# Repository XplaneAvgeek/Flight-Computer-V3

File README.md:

Flight Computer V3 is the third version of model rocket flight computers I've been trying to build. It's designed to control a guided model rocket, and improve things from V2.
<br><br>Some specs about it are:
  - Input Voltage: 6-17V
  - Uses a STM32H743VIH6 microcontroller
  - 4 MOSFETs connected to battery input, I recommend use it for less than 3A
  - 5V power regulator that can regulate 5A using a TPS565208DDCR
  - Should have reverse polarity protection (NOT TESTED)
  - IMU: LSM6DSO32, which is 6 axis
  - Barometer: LPS22HB
  - Magnetometer: IIS2MDC
  - Flash Memory: W25Q256JVEIQ TR, which is 32MB
  - Programming methods: ST-LINK V2, FS USB-C
  - Onboard Indication: 2 addressable RGB LEDs
  - Communication outside board: SPI, I2C, FDCAN, USART
  - Has 8 servo connectors at 5V but total 5V max is 5A

<br><br>[Here is the link to the code in Arduino Framework.](FlightComputerV3_Setup)
<br>[Here is the link to the KiCad design files.](Flight_Computer_V2_Proto2)

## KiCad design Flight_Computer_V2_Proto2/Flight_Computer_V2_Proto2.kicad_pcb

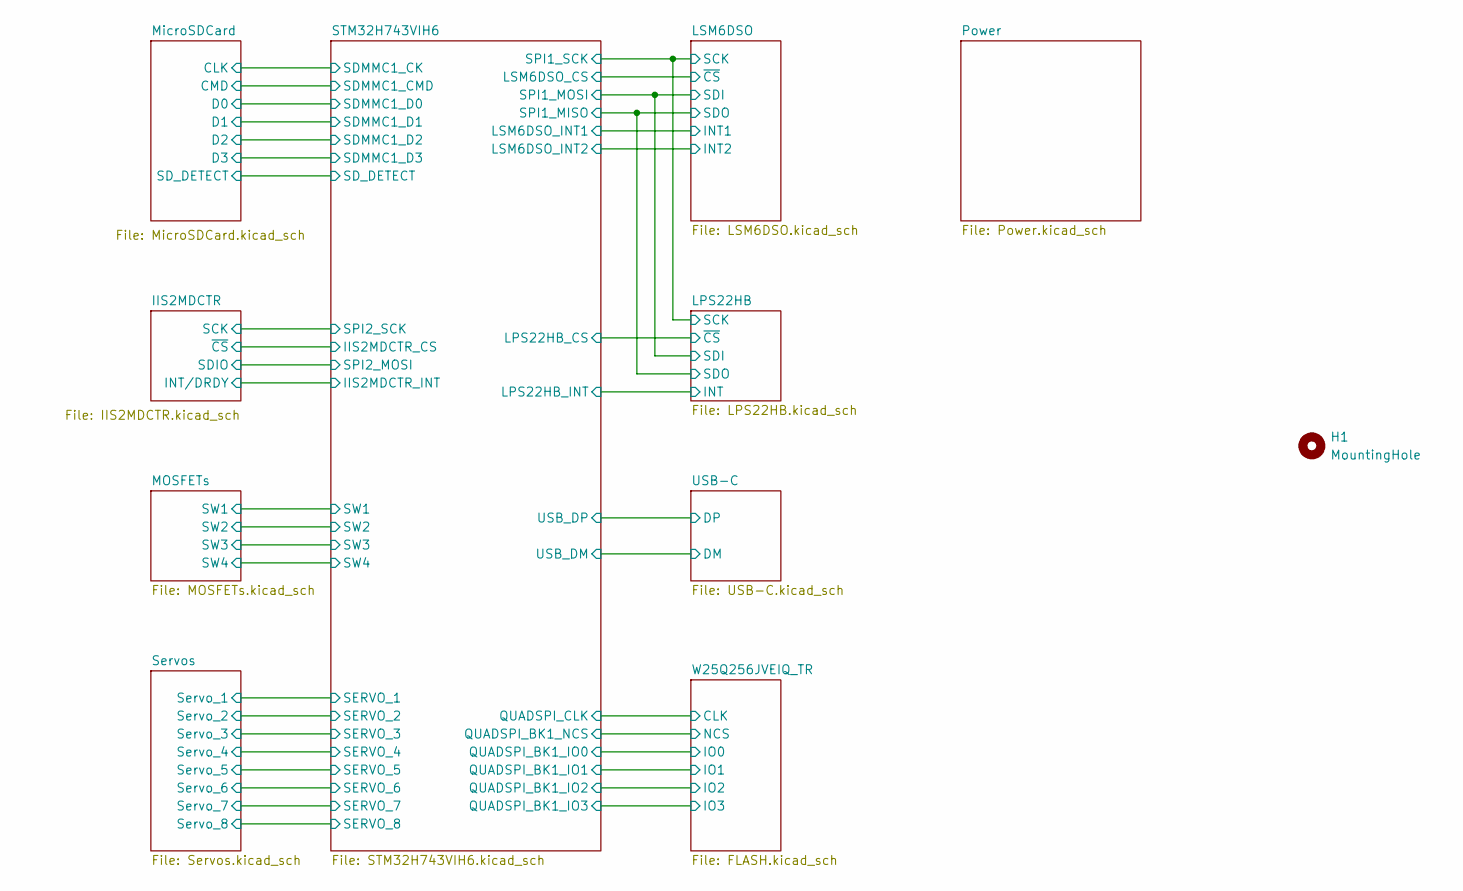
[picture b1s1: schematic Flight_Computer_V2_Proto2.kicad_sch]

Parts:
H1: MountingHole; logo15x15mmv3

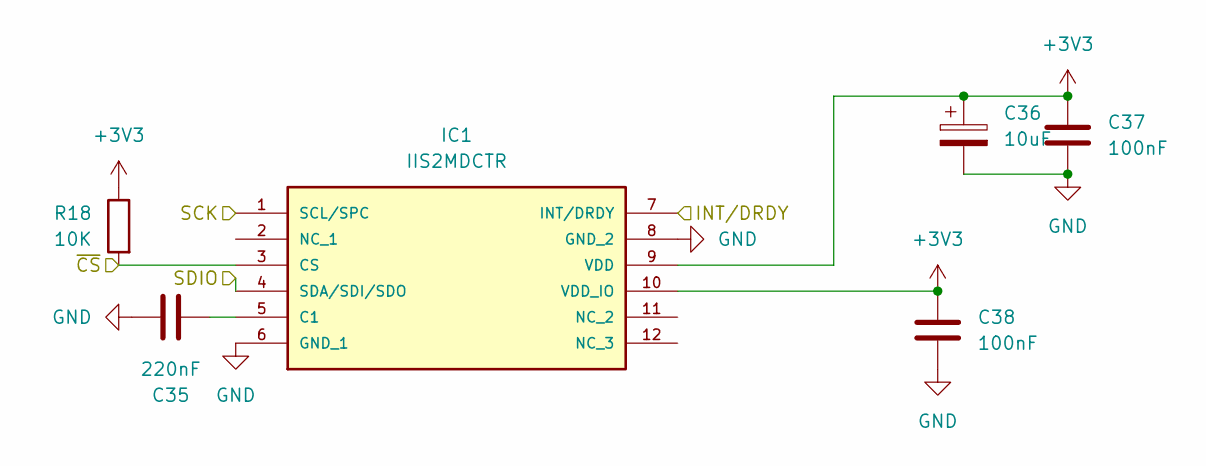
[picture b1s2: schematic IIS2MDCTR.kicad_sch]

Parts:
C35: 220nF; C_0402_1005Metric
C36: 10uF; CP_Elec_4x5.3
C37, C38: 100nF; C_0402_1005Metric
IC1: IIS2MDCTR; LGA-12_2x2mm_P0.5mm; MOUSER_PART_NUMBER 511-IIS2MDCTR
R18: 10K; R_0402_1005Metric

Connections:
+3V3: C36.1, C37.1, C38.1, IC1.9 (VDD), IC1.10 (VDD_IO), R18.1; also elsewhere on the board
/IIS2MDCTR/INT/DRDY: IC1.7 (INT/DRDY); also elsewhere on the board
/IIS2MDCTR/SCK: IC1.1 (SCL/SPC); also elsewhere on the board
/IIS2MDCTR/SDIO: IC1.4 (SDA/SDI/SDO); also elsewhere on the board
/IIS2MDCTR/~CS: IC1.3 (CS), R18.2; also elsewhere on the board
GND: C35.1, C36.2, C37.2, C38.2, IC1.6 (GND_1), IC1.8 (GND_2); also elsewhere on the board
unnamed: C35.2, IC1.5 (C1)

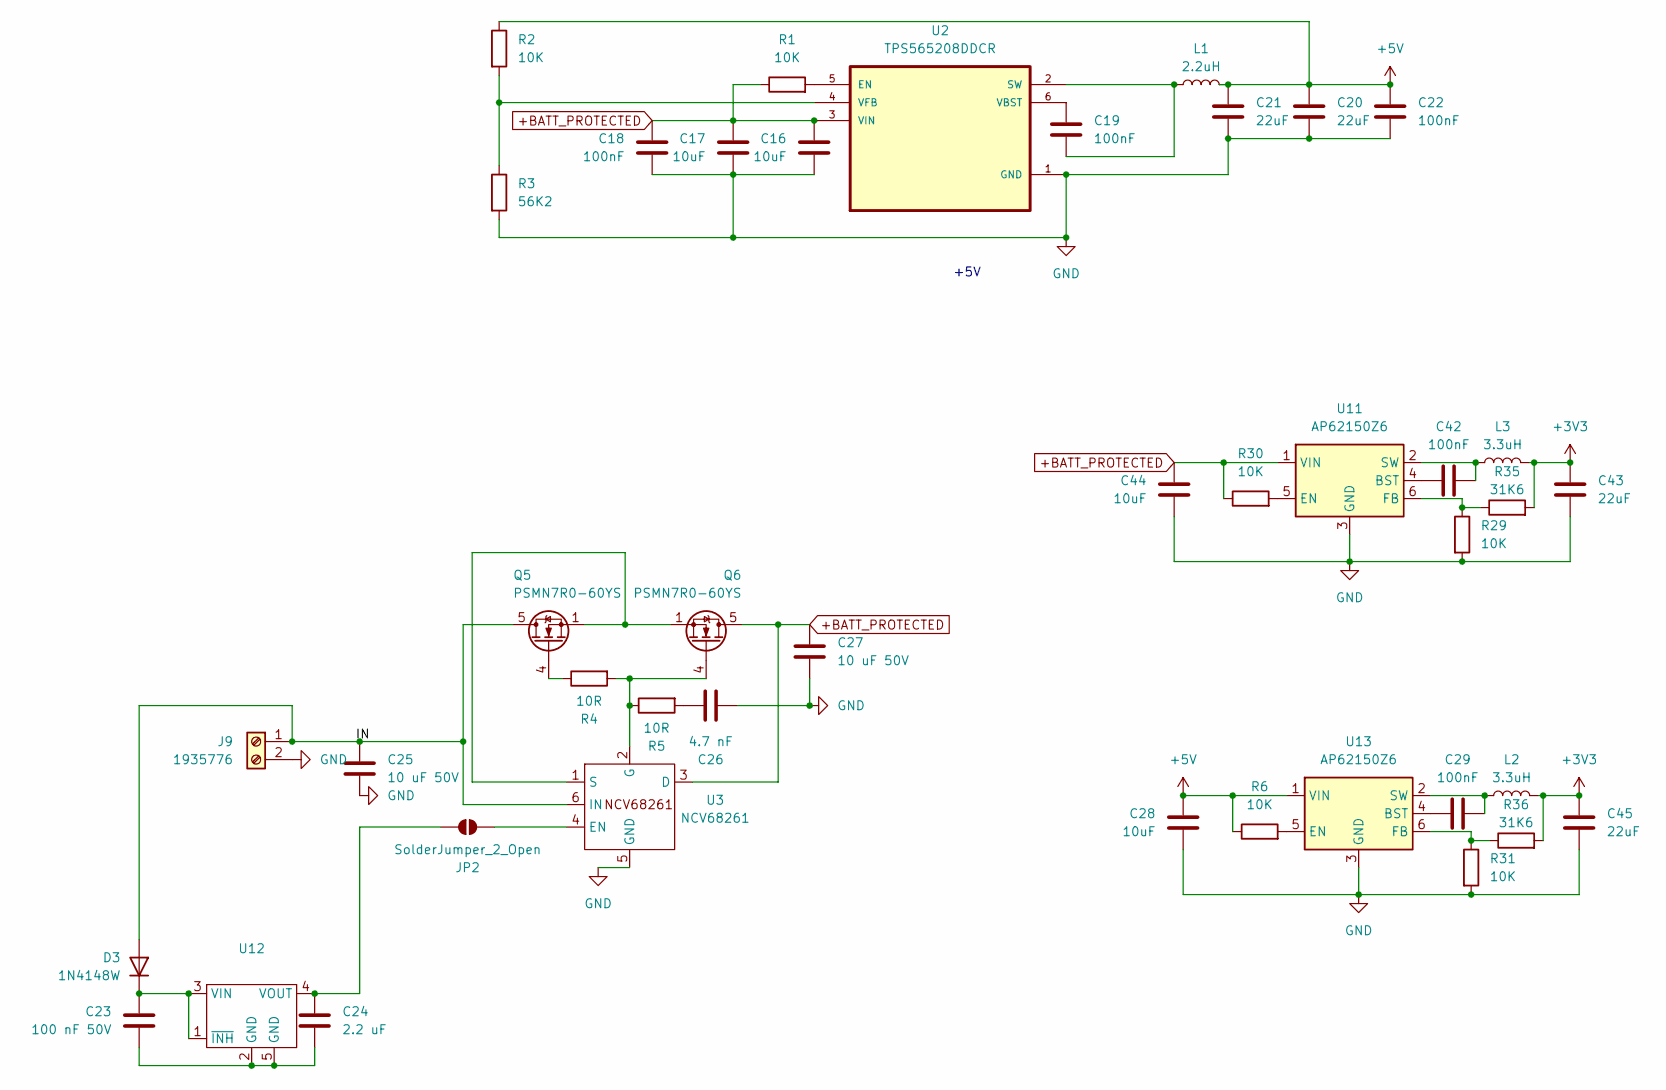
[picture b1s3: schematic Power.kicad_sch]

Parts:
C16, C17, C28, C44: 10uF; C_1206_3216Metric
C18, C19, C22, C29, C42: 100nF; C_0402_1005Metric
C20, C21, C43, C45: 22uF; C_1206_3216Metric
C23: 100 nF 50V; C_0603_1608Metric
C24: 2.2 uF; C_0805_2012Metric
C25, C27: 10 uF 50V; C_1206_3216Metric
C26: 4.7 nF; C_0603_1608Metric
D3: 1N4148W; D_SOD-123
J9: 1935776; PHOENIX_1935776
JP2: SolderJumper_2_Open; SolderJumper-2_P1.3mm_Open_TrianglePad1.0x1.5mm
L1: 2.2uH; L_Bourns_SRP5030T
L2, L3: 3.3uH; L_1008_2520Metric
Q5, Q6: PSMN7R0-60YS; LFPAK56
R1, R2, R6, R29, R30, R31: 10K; R_0402_1005Metric
R3: 56K2; R_0402_1005Metric
R4, R5: 10R; R_0603_1608Metric
R35, R36: 31K6; R_0402_1005Metric
U2: TPS565208DDCR; SOT95P280X110-6N
U3: NCV68261; DFN-6-1EP_2x2mm_P0.65mm_EP1x1.6mm
U11, U13: AP62150Z6; SOT-563
U12: NCV4296-2CSN50T1G; TSOP-5_1.65x3.05mm_P0.95mm

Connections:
+3V3: C43.1, C45.1, L2.2, L3.2, R35.2, R36.2; also elsewhere on the board
+5V: C20.1, C21.1, C22.1, C28.1, L1.2, R2.1, R6.1, U13.1 (VIN); also elsewhere on the board
+BATT_PROTECTED: C16.1, C17.1, C18.1, C27.1, C44.1, Q6.5 (D), R1.1, R30.1, U2.3 (VIN), U3.3 (D), U11.1 (VIN); also elsewhere on the board
/Power/IN: C25.1, D3.2 (A), J9.1, Q5.5 (D), U3.6 (IN)
GND: C16.2, C17.2, C18.2, C20.2, C21.2, C22.2, C25.2, C26.2, C27.2, C28.2, C43.2, C44.2, C45.2, J9.2, R3.2, R29.2, R31.2, U2.1 (GND), U3.5 (GND), U11.3 (GND), U13.3 (GND); also elsewhere on the board
unnamed: C23.2, C24.2, U12.2 (GND), U12.5 (GND)
unnamed: C26.1, R5.2
unnamed: C23.1, D3.1 (K), U12.1 (~INH), U12.3 (VIN)
unnamed: JP2.1 (A), U3.4 (EN)
unnamed: C24.1, JP2.2 (B), U12.4 (VOUT)
unnamed: Q5.4 (G), R4.1
unnamed: Q6.4 (G), R4.2, R5.1, U3.2 (G)
unnamed: R1.2, U2.5 (EN)
unnamed: C19.2, L1.1, U2.2 (SW)
unnamed: C19.1, U2.6 (VBST)
unnamed: R2.2, R3.1, U2.4 (VFB)
unnamed: Q5.1 (S), Q5.2 (S), Q5.3 (S), Q6.1 (S), Q6.2 (S), Q6.3 (S), U3.1 (S)
unnamed: C42.1, U11.4 (BST)
unnamed: R30.2, U11.5 (EN)
unnamed: R29.1, R35.1, U11.6 (FB)
unnamed: C42.2, L3.1, U11.2 (SW)
unnamed: C29.1, U13.4 (BST)
unnamed: R6.2, U13.5 (EN)
unnamed: R31.1, R36.1, U13.6 (FB)
unnamed: C29.2, L2.1, U13.2 (SW)

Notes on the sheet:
+5V

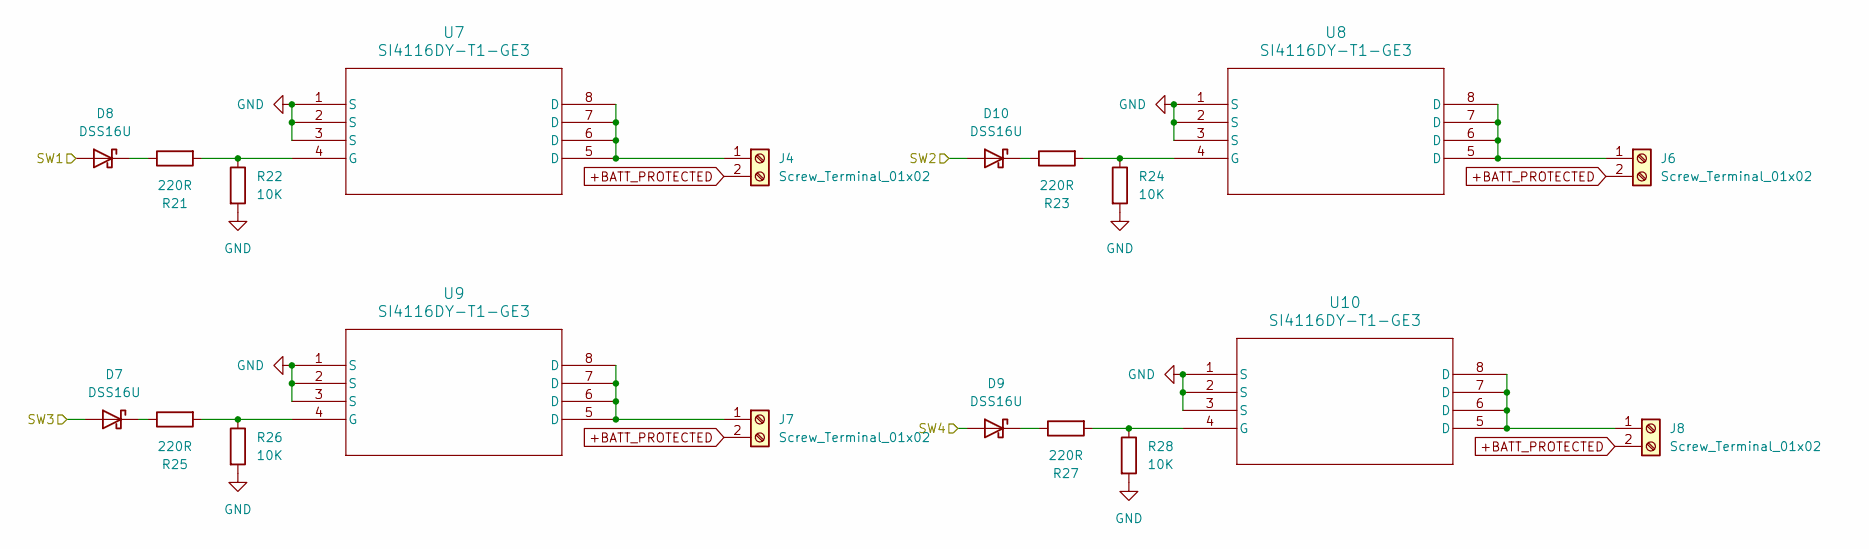
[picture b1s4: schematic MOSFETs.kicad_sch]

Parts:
D7, D8, D9, D10: DSS16U; D_SOD-123F
J4, J6, J7, J8: Screw_Terminal_01x02; PHOENIX_1935776
R21, R23, R25, R27: 220R; R_0402_1005Metric
R22, R24, R26, R28: 10K; R_0402_1005Metric
U7, U8, U9, U10: SI4116DY-T1-GE3; SOIC-8_3.9x4.9mm_P1.27mm

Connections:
+BATT_PROTECTED: J4.2, J6.2, J7.2, J8.2; also elsewhere on the board
/MOSFETs/SW1: D8.2 (A); also elsewhere on the board
/MOSFETs/SW2: D10.2 (A); also elsewhere on the board
/MOSFETs/SW3: D7.2 (A); also elsewhere on the board
/MOSFETs/SW4: D9.2 (A); also elsewhere on the board
GND: R22.2, R24.2, R26.2, R28.2, U7.1 (S), U7.2 (S), U7.3 (S), U8.1 (S), U8.2 (S), U8.3 (S), U9.1 (S), U9.2 (S), U9.3 (S), U10.1 (S), U10.2 (S), U10.3 (S); also elsewhere on the board
unnamed: D7.1 (K), R25.1
unnamed: D8.1 (K), R21.1
unnamed: D9.1 (K), R27.1
unnamed: D10.1 (K), R23.1
unnamed: J4.1, U7.5 (D), U7.6 (D), U7.7 (D), U7.8 (D)
unnamed: J6.1, U8.5 (D), U8.6 (D), U8.7 (D), U8.8 (D)
unnamed: J7.1, U9.5 (D), U9.6 (D), U9.7 (D), U9.8 (D)
unnamed: J8.1, U10.5 (D), U10.6 (D), U10.7 (D), U10.8 (D)
unnamed: R21.2, R22.1, U7.4 (G)
unnamed: R23.2, R24.1, U8.4 (G)
unnamed: R25.2, R26.1, U9.4 (G)
unnamed: R27.2, R28.1, U10.4 (G)

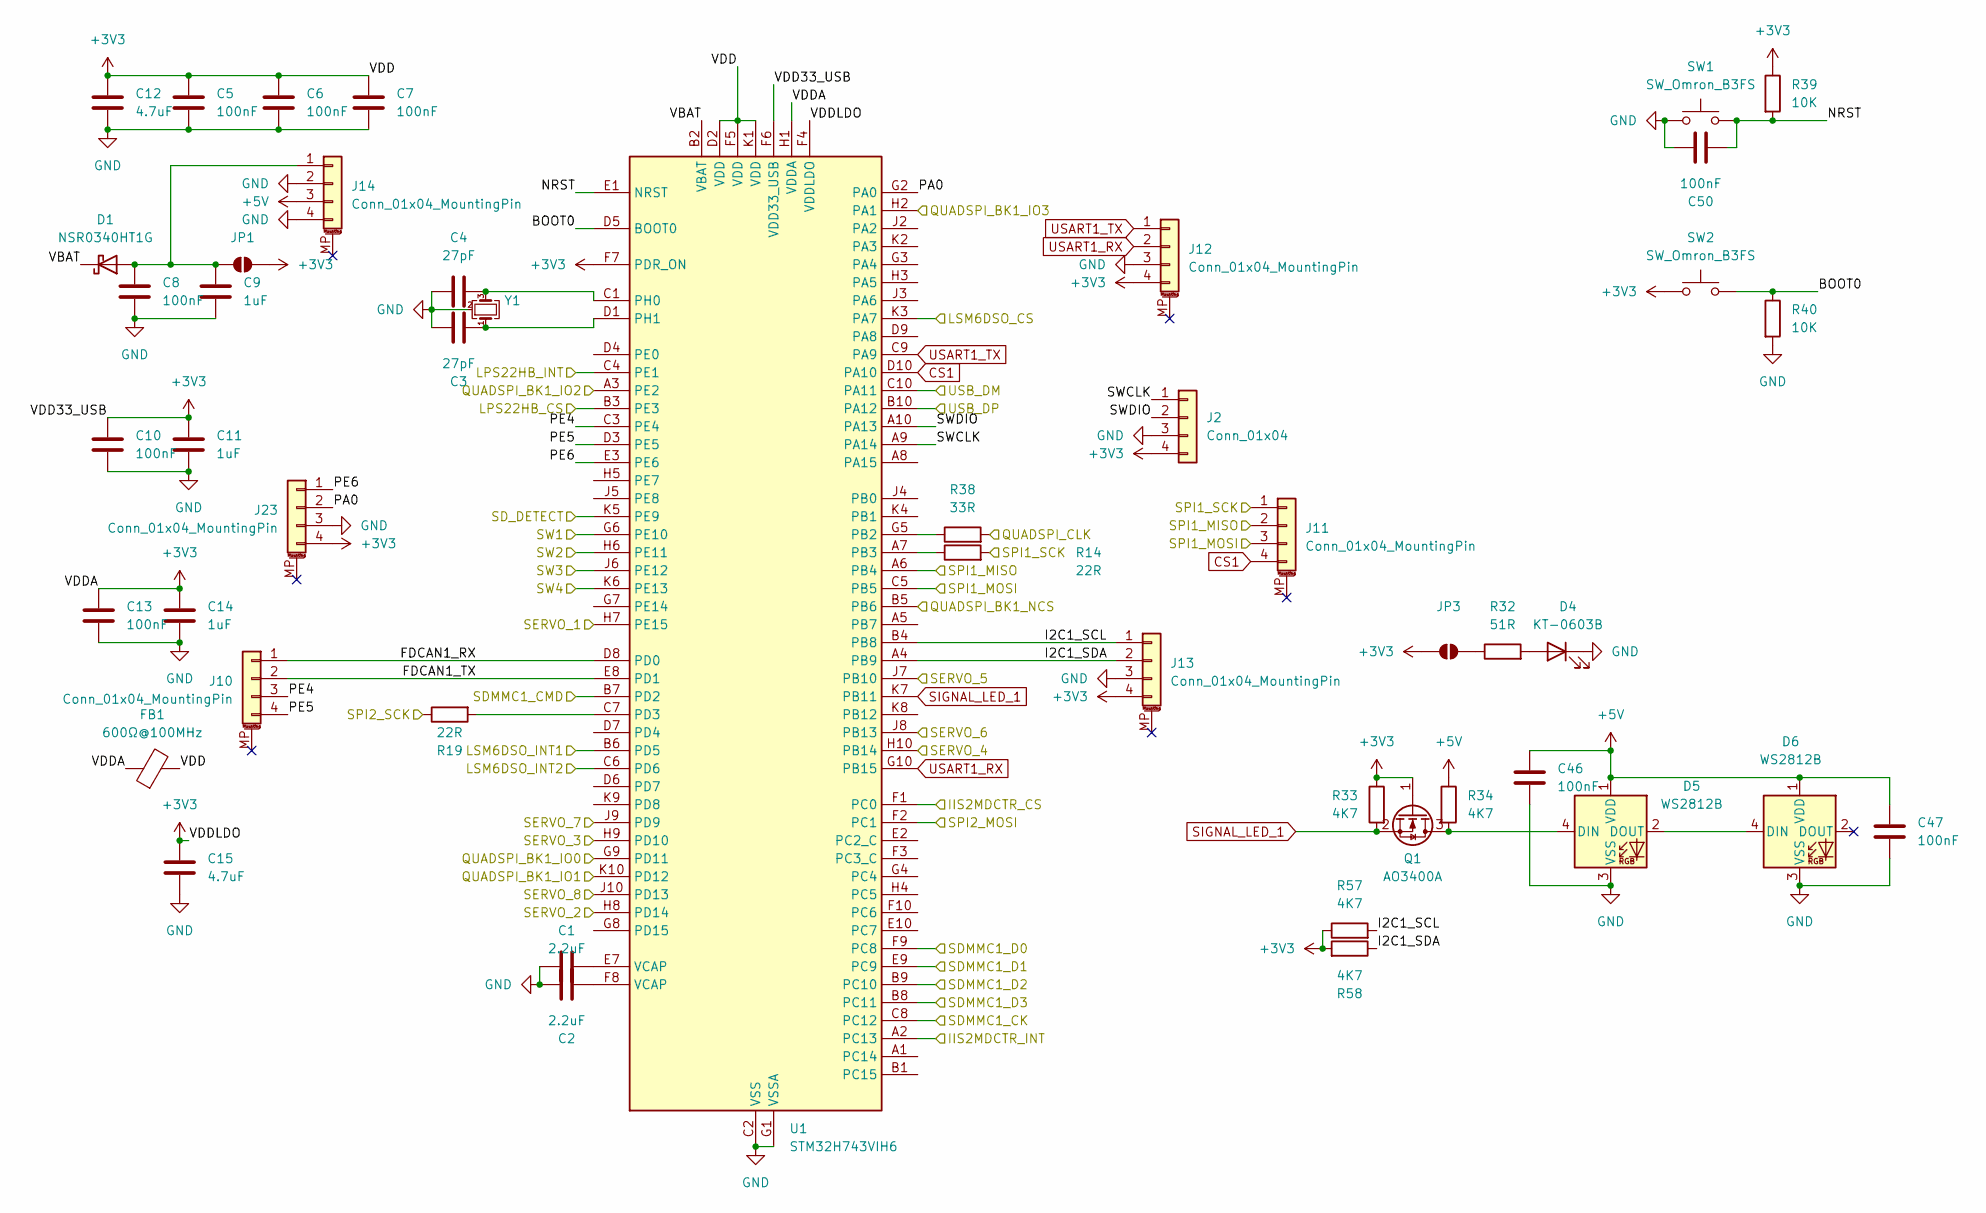
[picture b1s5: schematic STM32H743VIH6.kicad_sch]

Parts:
C1, C2: 2.2uF; C_0805_2012Metric
C3, C4: 27pF; C_0402_1005Metric
C5, C6, C7, C8, C10, C13, C46, C47, C50: 100nF; C_0402_1005Metric
C9, C11, C14: 1uF; C_0603_1608Metric
C12, C15: 4.7uF; C_0805_2012Metric
D1: NSR0340HT1G; D_SOD-323
D4: KT-0603B; LED_0603_1608Metric
D5, D6: WS2812B; LED_WS2812B_PLCC4_5.0x5.0mm_P3.2mm
FB1: 600Ω@100MHz; L_0603_1608Metric
J2: Conn_01x04; PinHeader_1x04_P2.54mm_Vertical
J10, J11, J12, J13, J14, J23: Conn_01x04_MountingPin; JST_SH_SM04B-SRSS-TB_1x04-1MP_P1.00mm_Horizontal
JP1, JP3: SolderJumper_2_Open; SolderJumper-2_P1.3mm_Open_TrianglePad1.0x1.5mm
Q1: AO3400A; SOT-23
R14, R19: 22R; R_0402_1005Metric
R32: 51R; R_0402_1005Metric
R33, R34, R57, R58: 4K7; R_0402_1005Metric
R38: 33R; R_0402_1005Metric
R39, R40: 10K; R_0402_1005Metric
SW1, SW2: SW_Omron_B3FS; SW_SPST_Omron_B3FS-101xP
U1: STM32H743VIH6; TFBGA-100_8x8mm_Layout10x10_P0.8mm
Y1: ABM3B-8.000MHZ-B2-T; Crystal_SMD_5032-4Pin_5.0x3.2mm

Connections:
+3V3: C5.1, C6.1, C7.1, C10.1, C11.1, C12.2, C13.1, C14.1, C15.2, FB1.1, FB1.2, J2.4, J12.4, J13.4, J23.4, JP1.1 (A), JP3.1 (A), Q1.1 (G), R33.1, R39.1, R57.1, R58.2, SW2.1, U1.D2 (VDD), U1.F4 (VDDLDO), U1.F5 (VDD), U1.F6 (VDD33_USB), U1.F7 (PDR_ON), U1.H1 (VDDA), U1.K1 (VDD); also elsewhere on the board
+5V: C46.1, C47.1, D5.1 (VDD), D6.1 (VDD), J14.3, R34.1; also elsewhere on the board
/IIS2MDCTR/INT/DRDY: U1.A2 (PC13); also elsewhere on the board
/IIS2MDCTR/SCK: R19.1; also elsewhere on the board
/IIS2MDCTR/SDIO: U1.F2 (PC1); also elsewhere on the board
/IIS2MDCTR/~CS: U1.F1 (PC0); also elsewhere on the board
/LPS22HB/INT: U1.C4 (PE1); also elsewhere on the board
/LPS22HB/SCK: J11.1, R14.2; also elsewhere on the board
/LPS22HB/SDI: J11.3, U1.C5 (PB5); also elsewhere on the board
/LPS22HB/SDO: J11.2, U1.A6 (PB4); also elsewhere on the board
/LPS22HB/~CS: U1.B3 (PE3); also elsewhere on the board
/LSM6DSO/INT1: U1.B6 (PD5); also elsewhere on the board
/LSM6DSO/INT2: U1.C6 (PD6); also elsewhere on the board
/LSM6DSO/~CS: U1.K3 (PA7); also elsewhere on the board
/MOSFETs/SW1: U1.G6 (PE10); also elsewhere on the board
/MOSFETs/SW2: U1.H6 (PE11); also elsewhere on the board
/MOSFETs/SW3: U1.J6 (PE12); also elsewhere on the board
/MOSFETs/SW4: U1.K6 (PE13); also elsewhere on the board
/MicroSDCard/CLK: U1.C8 (PC12); also elsewhere on the board
/MicroSDCard/CMD: U1.B7 (PD2); also elsewhere on the board
/MicroSDCard/D0: U1.F9 (PC8); also elsewhere on the board
/MicroSDCard/D1: U1.E9 (PC9); also elsewhere on the board
/MicroSDCard/D2: U1.B9 (PC10); also elsewhere on the board
/MicroSDCard/D3: U1.B8 (PC11); also elsewhere on the board
/MicroSDCard/SD_DETECT: U1.K5 (PE9); also elsewhere on the board
/STM32H743VIH6/BOOT0: R40.1, SW2.2, U1.D5 (BOOT0)
/STM32H743VIH6/FDCAN1_RX: J10.1, U1.D8 (PD0)
/STM32H743VIH6/FDCAN1_TX: J10.2, U1.E8 (PD1)
/STM32H743VIH6/I2C1_SCL: J13.1, R57.2, U1.B4 (PB8)
/STM32H743VIH6/I2C1_SDA: J13.2, R58.1, U1.A4 (PB9)
/STM32H743VIH6/NRST: C50.2, R39.2, SW1.2, U1.E1 (NRST)
/STM32H743VIH6/PA0: J23.2, U1.G2 (PA0)
/STM32H743VIH6/PE4: J10.3, U1.C3 (PE4)
/STM32H743VIH6/PE5: J10.4, U1.D3 (PE5)
/STM32H743VIH6/PE6: J23.1, U1.E3 (PE6)
/STM32H743VIH6/QUADSPI_BK1_IO0: U1.G9 (PD11); also elsewhere on the board
/STM32H743VIH6/QUADSPI_BK1_IO1: U1.K10 (PD12); also elsewhere on the board
/STM32H743VIH6/QUADSPI_BK1_IO2: U1.A3 (PE2); also elsewhere on the board
/STM32H743VIH6/QUADSPI_BK1_IO3: U1.H2 (PA1); also elsewhere on the board
/STM32H743VIH6/QUADSPI_BK1_NCS: U1.B5 (PB6); also elsewhere on the board
/STM32H743VIH6/QUADSPI_CLK: R38.2; also elsewhere on the board
/STM32H743VIH6/SERVO_1: U1.H7 (PE15); also elsewhere on the board
/STM32H743VIH6/SERVO_2: U1.H8 (PD14); also elsewhere on the board
/STM32H743VIH6/SERVO_3: U1.H9 (PD10); also elsewhere on the board
/STM32H743VIH6/SERVO_4: U1.H10 (PB14); also elsewhere on the board
/STM32H743VIH6/SERVO_5: U1.J7 (PB10); also elsewhere on the board
/STM32H743VIH6/SERVO_6: U1.J8 (PB13); also elsewhere on the board
/STM32H743VIH6/SERVO_7: U1.J9 (PD9); also elsewhere on the board
/STM32H743VIH6/SERVO_8: U1.J10 (PD13); also elsewhere on the board
/STM32H743VIH6/SWCLK: J2.1, U1.A9 (PA14)
/STM32H743VIH6/SWDIO: J2.2, U1.A10 (PA13)
/STM32H743VIH6/USB_DM: U1.C10 (PA11); also elsewhere on the board
/STM32H743VIH6/USB_DP: U1.B10 (PA12); also elsewhere on the board
/STM32H743VIH6/VBAT: D1.1 (K), U1.B2 (VBAT)
CS1: J11.4, U1.D10 (PA10)
GND: C1.1, C2.1, C3.1, C4.1, C5.2, C6.2, C7.2, C8.2, C9.2, C10.2, C11.2, C12.1, C13.2, C14.2, C15.1, C46.2, C47.2, C50.1, D4.1 (K), D5.3 (VSS), D6.3 (VSS), J2.3, J12.3, J13.3, J14.2, J14.4, J23.3, R40.2, SW1.1, U1.C2 (VSS), U1.E4 (VSS), U1.E5 (VSS), U1.E6 (VSS), U1.G1 (VSSA), U1.J1 (VSS), Y1.2 (G), Y1.4 (G); also elsewhere on the board
unnamed: C1.2, U1.E7 (VCAP)
unnamed: C2.2, U1.F8 (VCAP)
unnamed: C8.1, C9.1, D1.2 (A), J14.1, JP1.2 (B)
unnamed: D4.2 (A), R32.2
unnamed: D5.4 (DIN), Q1.3 (D), R34.2
unnamed: D5.2 (DOUT), D6.4 (DIN)
unnamed: JP3.2 (B), R32.1
unnamed: R38.1, U1.G5 (PB2)
unnamed: R14.1, U1.A7 (PB3)
unnamed: R19.2, U1.C7 (PD3)
unnamed: C4.2, U1.C1 (PH0), Y1.3
unnamed: C3.2, U1.D1 (PH1), Y1.1
SIGNAL_LED_1: Q1.2 (S), R33.2, U1.K7 (PB11)
USART1_RX: J12.2, U1.G10 (PB15)
USART1_TX: J12.1, U1.C9 (PA9)

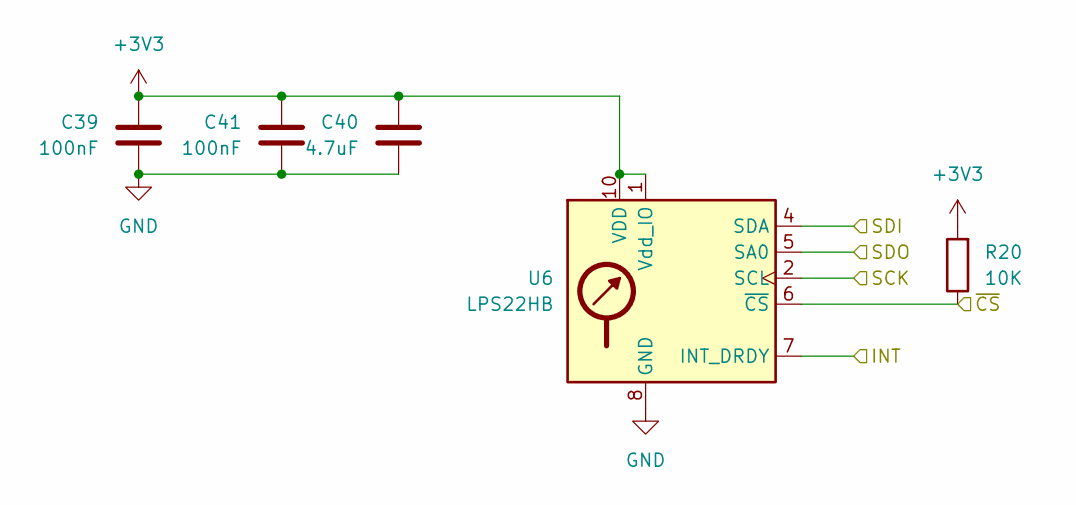
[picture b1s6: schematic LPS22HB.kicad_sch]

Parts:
C39, C41: 100nF; C_0402_1005Metric
C40: 4.7uF; C_0805_2012Metric
R20: 10K; R_0402_1005Metric
U6: LPS22HB; ST_HLGA-10_2x2mm_P0.5mm_LayoutBorder3x2y

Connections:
+3V3: C39.1, C40.1, C41.1, R20.2, U6.1 (Vdd_IO), U6.10 (VDD); also elsewhere on the board
/LPS22HB/INT: U6.7 (INT_DRDY); also elsewhere on the board
/LPS22HB/SCK: U6.2 (SCL); also elsewhere on the board
/LPS22HB/SDI: U6.4 (SDA); also elsewhere on the board
/LPS22HB/SDO: U6.5 (SA0); also elsewhere on the board
/LPS22HB/~CS: R20.1, U6.6 (~CS); also elsewhere on the board
GND: C39.2, C40.2, C41.2, U6.3 (GND), U6.8 (GND), U6.9 (GND); also elsewhere on the board

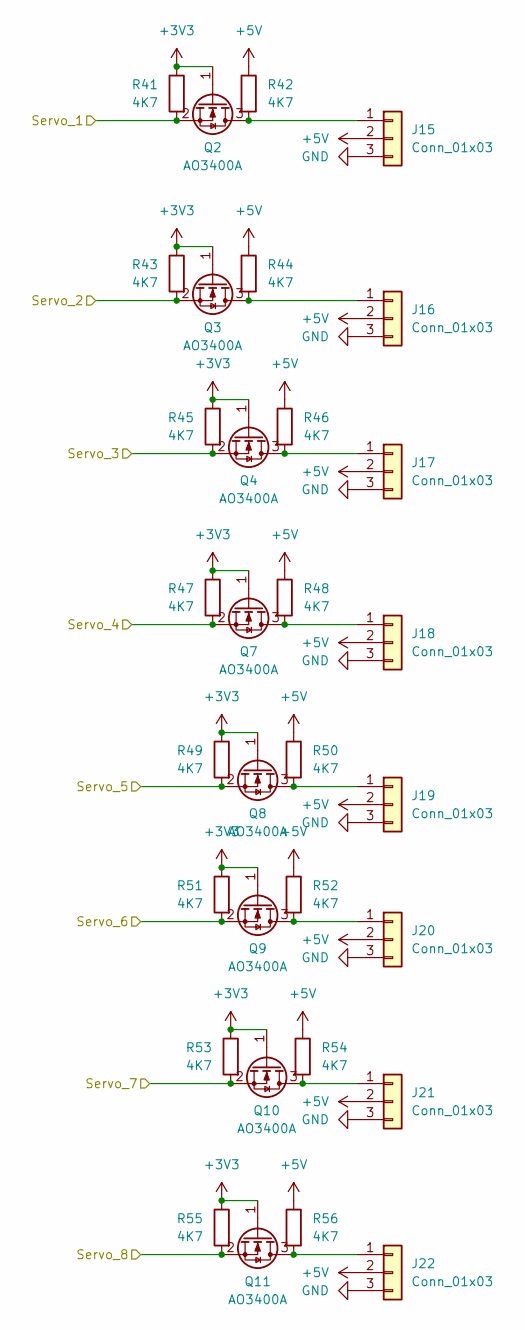
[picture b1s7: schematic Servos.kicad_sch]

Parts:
J15, J16, J17, J18, J19, J20, J21, J22: Conn_01x03; PinHeader_1x03_P2.54mm_Vertical
Q2, Q3, Q4, Q7, Q8, Q9, Q10, Q11: AO3400A; SOT-23
R41, R42, R43, R44, R45, R46, R47, R48, R49, R50, R51, R52, R53, R54, R55, R56: 4K7; R_0402_1005Metric

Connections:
+3V3: Q2.1 (G), Q3.1 (G), Q4.1 (G), Q7.1 (G), Q8.1 (G), Q9.1 (G), Q10.1 (G), Q11.1 (G), R41.1, R43.1, R45.1, R47.1, R49.1, R51.1, R53.1, R55.1; also elsewhere on the board
+5V: J15.2, J16.2, J17.2, J18.2, J19.2, J20.2, J21.2, J22.2, R42.1, R44.1, R46.1, R48.1, R50.1, R52.1, R54.1, R56.1; also elsewhere on the board
/STM32H743VIH6/SERVO_1: Q2.2 (S), R41.2; also elsewhere on the board
/STM32H743VIH6/SERVO_2: Q3.2 (S), R43.2; also elsewhere on the board
/STM32H743VIH6/SERVO_3: Q4.2 (S), R45.2; also elsewhere on the board
/STM32H743VIH6/SERVO_4: Q7.2 (S), R47.2; also elsewhere on the board
/STM32H743VIH6/SERVO_5: Q8.2 (S), R49.2; also elsewhere on the board
/STM32H743VIH6/SERVO_6: Q9.2 (S), R51.2; also elsewhere on the board
/STM32H743VIH6/SERVO_7: Q10.2 (S), R53.2; also elsewhere on the board
/STM32H743VIH6/SERVO_8: Q11.2 (S), R55.2; also elsewhere on the board
GND: J15.3, J16.3, J17.3, J18.3, J19.3, J20.3, J21.3, J22.3; also elsewhere on the board
unnamed: J15.1, Q2.3 (D), R42.2
unnamed: J16.1, Q3.3 (D), R44.2
unnamed: J17.1, Q4.3 (D), R46.2
unnamed: J18.1, Q7.3 (D), R48.2
unnamed: J19.1, Q8.3 (D), R50.2
unnamed: J20.1, Q9.3 (D), R52.2
unnamed: J21.1, Q10.3 (D), R54.2
unnamed: J22.1, Q11.3 (D), R56.2

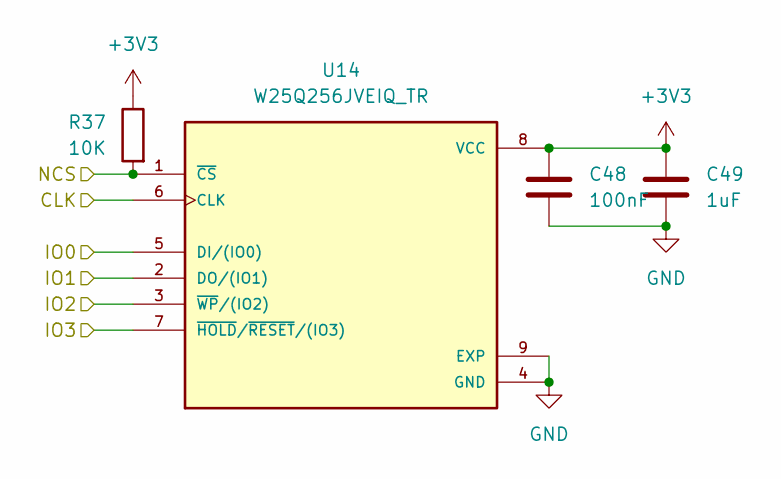
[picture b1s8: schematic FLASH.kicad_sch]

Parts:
C48: 100nF; C_0402_1005Metric
C49: 1uF; C_0603_1608Metric
R37: 10K; R_0402_1005Metric
U14: W25Q256JVEIQ_TR; SON127P600X800X80-9N; PARTREV G

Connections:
+3V3: C48.1, C49.1, R37.1, U14.8 (VCC); also elsewhere on the board
/STM32H743VIH6/QUADSPI_BK1_IO0: U14.5 (DI/(IO0)); also elsewhere on the board
/STM32H743VIH6/QUADSPI_BK1_IO1: U14.2 (DO/(IO1)); also elsewhere on the board
/STM32H743VIH6/QUADSPI_BK1_IO2: U14.3 (~WP/(IO2)); also elsewhere on the board
/STM32H743VIH6/QUADSPI_BK1_IO3: U14.7 (~HOLD/~RESET/(IO3)); also elsewhere on the board
/STM32H743VIH6/QUADSPI_BK1_NCS: R37.2, U14.1 (~CS); also elsewhere on the board
/STM32H743VIH6/QUADSPI_CLK: U14.6 (CLK); also elsewhere on the board
GND: C48.2, C49.2, U14.4 (GND), U14.9 (EXP); also elsewhere on the board

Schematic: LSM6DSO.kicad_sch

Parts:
C33, C34: 100nF; C_0402_1005Metric
R17: 10K; R_0402_1005Metric
U4: LSM6DSO; LGA-14_3x2.5mm_P0.5mm_LayoutBorder3x4y

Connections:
+3V3: C33.1, C34.1, R17.2, U4.2 (SDIX), U4.3 (SCX), U4.5 (VDDIO), U4.8 (VDD); also elsewhere on the board
/LPS22HB/SCK: U4.13 (SCL); also elsewhere on the board
/LPS22HB/SDI: U4.14 (SDA); also elsewhere on the board
/LPS22HB/SDO: U4.1 (SDO/SA0); also elsewhere on the board
/LSM6DSO/INT1: U4.4 (INT1); also elsewhere on the board
/LSM6DSO/INT2: U4.9 (INT2); also elsewhere on the board
/LSM6DSO/~CS: R17.1, U4.12 (~CS); also elsewhere on the board
GND: C33.2, C34.2, U4.6 (GND@6), U4.7 (GND@7); also elsewhere on the board

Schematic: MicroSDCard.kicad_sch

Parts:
C30: 10uF; CP_Elec_4x5.3
C31: 100nF; C_0402_1005Metric
C32: 1uF; C_0603_1608Metric
J1: Micro_SD_Card_Det_Hirose_DM3AT; microSD_HC_Hirose_DM3D-SF
R7, R8, R9, R10, R11: 47K; R_0402_1005Metric
R12: 33R; R_0402_1005Metric
R13: 10K; R_0402_1005Metric

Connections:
+3V3: C30.1, C31.1, C32.1, J1.4 (VDD), R7.1, R8.1, R9.1, R10.1, R11.1, R13.1; also elsewhere on the board
/MicroSDCard/CLK: R12.1; also elsewhere on the board
/MicroSDCard/CMD: J1.3 (CMD), R9.2; also elsewhere on the board
/MicroSDCard/D0: J1.7 (DAT0), R8.2; also elsewhere on the board
/MicroSDCard/D1: J1.8 (DAT1), R7.2; also elsewhere on the board
/MicroSDCard/D2: J1.1 (DAT2), R11.2; also elsewhere on the board
/MicroSDCard/D3: J1.2 (DAT3/CD), R10.2; also elsewhere on the board
/MicroSDCard/SD_DETECT: J1.9 (DET_B), R13.2; also elsewhere on the board
GND: C30.2, C31.2, C32.2, J1.6 (VSS), J1.10 (DET_A), J1.11 (SHIELD); also elsewhere on the board
unnamed: J1.5 (CLK), R12.2

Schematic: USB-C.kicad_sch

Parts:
D2: DSS16U; D_SOD-123F
J3: USB_C_Receptacle_USB2.0_16P; USB_C_Receptacle_GCT_USB4110
R15, R16: 5K1; R_0402_1005Metric
U5: USBLC6-2SC6; SOT-23-6

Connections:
+5V: D2.1 (K); also elsewhere on the board
/STM32H743VIH6/USB_DM: U5.6 (I/O1); also elsewhere on the board
/STM32H743VIH6/USB_DP: U5.4 (I/O2); also elsewhere on the board
GND: J3.A1 (GND), J3.A12 (GND), J3.B1 (GND), J3.B12 (GND), J3.S1 (SHIELD), R15.2, R16.2, U5.2 (GND); also elsewhere on the board
unnamed: D2.2 (A), J3.A4 (VBUS), J3.A9 (VBUS), J3.B4 (VBUS), J3.B9 (VBUS), U5.5 (VBUS)
unnamed: J3.A5 (CC1), R15.1
unnamed: J3.B5 (CC2), R16.1
unnamed: J3.A6 (D+), J3.B6 (D+), U5.3 (I/O2)
unnamed: J3.A7 (D-), J3.B7 (D-), U5.1 (I/O1)

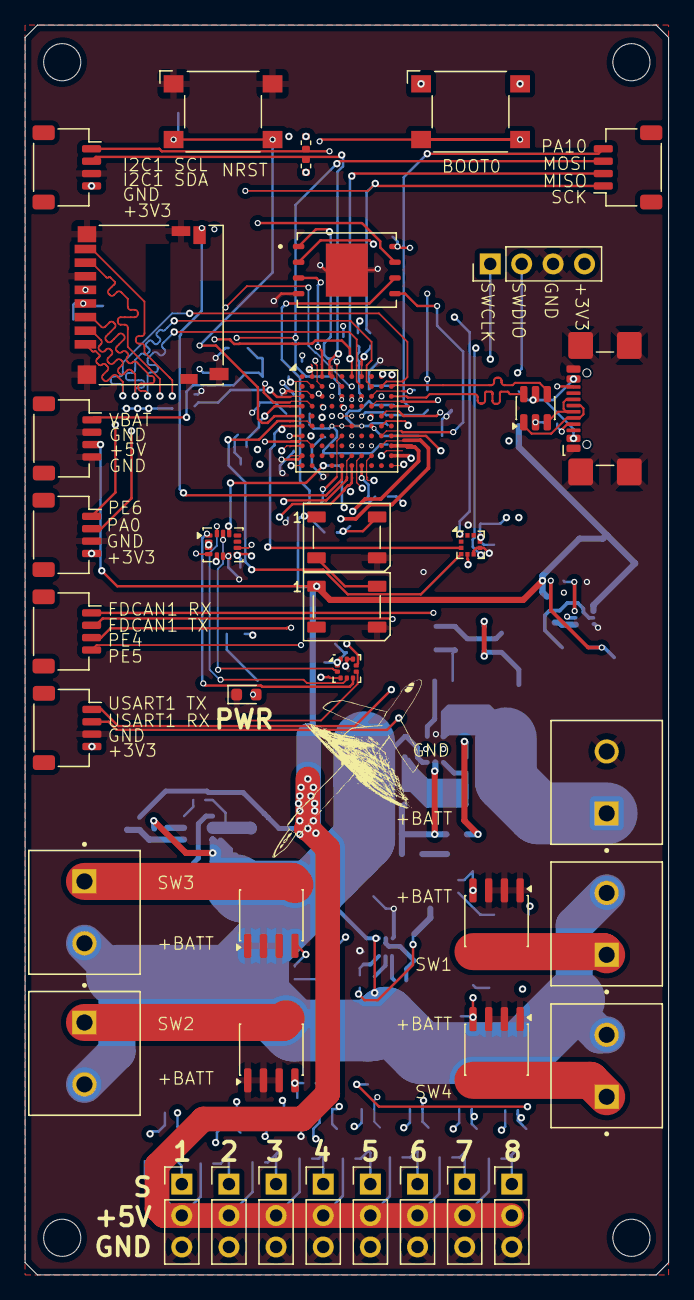
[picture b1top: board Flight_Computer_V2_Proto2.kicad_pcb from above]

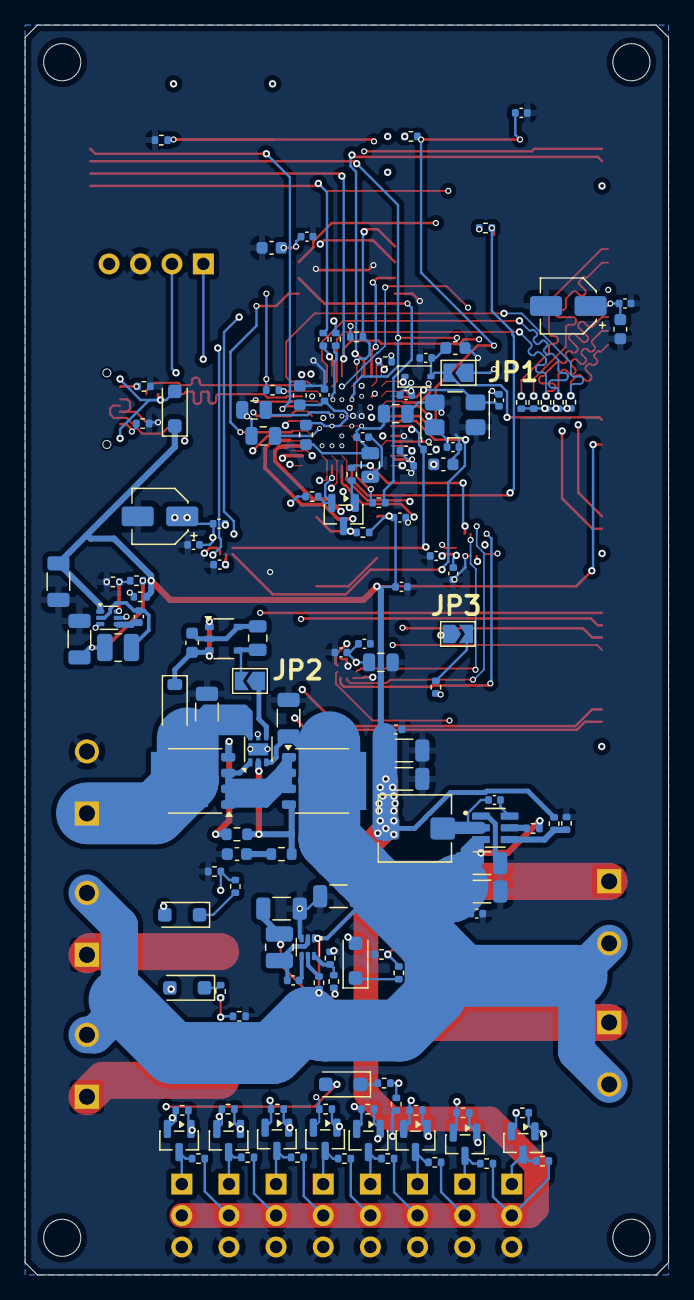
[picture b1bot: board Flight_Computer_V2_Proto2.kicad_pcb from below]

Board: 6 copper layers, 52.0 x 101.0 mm, 177 parts (137 on the bottom side), 120 nets.

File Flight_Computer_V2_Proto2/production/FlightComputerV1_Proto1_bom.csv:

Designator,Footprint,Quantity,Value,LCSC Part #
"C1, C2",0805,2,2.2uF,
"C10, C13, C18, C19, C22, C29, C31, C33, C34, C37, C38, C39, C41, C42, C46, C47, C48, C5, C50, C6, C7, C8",0402,22,100nF,
"C11, C14, C32, C49, C9",0603,5,1uF,
"C12, C15, C40",0805,3,4.7uF,
"C16, C17, C28, C44",1206,4,10uF,
"C20, C21, C43, C45",1206,4,22uF,
C23,0603,1,100 nF 50V,
C24,0805,1,2.2 uF,
"C25, C27",1206,2,10 uF 50V,
C26,0603,1,4.7 nF,
"C3, C4",0402,2,27pF,
"C30, C36",CP_Elec_4x5.3,2,10uF,
C35,0402,1,220nF,
D1,D_SOD-323,1,NSR0340HT1G,
"D10, D2, D7, D8, D9",D_SOD-123F,5,DSS16U,
D3,D_SOD-123,1,1N4148W,
D4,0603,1,KT-0603B,
"D5, D6",LED_WS2812B_PLCC4_5.0x5.0mm_P3.2mm,2,WS2812B,
FB1,0603,1,600Ω@100MHz,
IC1,LGA-12_2x2mm_P0.5mm,1,IIS2MDCTR,
J1,microSD_HC_Hirose_DM3D-SF,1,Micro_SD_Card_Det_Hirose_DM3AT,
"J10, J11, J12, J13, J14, J23",JST_SH_SM04B-SRSS-TB_1x04-1MP_P1.00mm_Horizontal,6,Conn_01x04_MountingPin,
"J15, J16, J17, J18, J19, J20, J21, J22",PinHeader_1x03_P2.54mm_Vertical,8,Conn_01x03,
J2,PinHeader_1x04_P2.54mm_Vertical,1,Conn_01x04,
J3,USB_C_Receptacle_GCT_USB4110,1,USB_C_Receptacle_USB2.0_16P,
"J4, J6, J7, J8",PHOENIX_1935776,4,Screw_Terminal_01x02,
J9,PHOENIX_1935776,1,1935776,
L1,L_Bourns_SRP5030T,1,2.2uH,
"L2, L3",1008,2,3.3uH,
"Q1, Q10, Q11, Q2, Q3, Q4, Q7, Q8, Q9",SOT-23,9,AO3400A,
"Q5, Q6",LFPAK56,2,PSMN7R0-60YS,
"R1, R13, R17, R18, R2, R20, R22, R24, R26, R28, R29, R30, R31, R37, R39, R40, R6",0402,17,10K,
"R10, R11, R7, R8, R9",0402,5,47K,
"R12, R38",0402,2,33R,
"R14, R19",0402,2,22R,
"R15, R16",0402,2,5K1,
"R21, R23, R25, R27",0402,4,220R,
R3,0402,1,56K2,
R32,0402,1,51R,
"R33, R34, R41, R42, R43, R44, R45, R46, R47, R48, R49, R50, R51, R52, R53, R54, R55, R56, R57, R58",0402,20,4K7,
"R35, R36",0402,2,31K6,
"R4, R5",0603,2,10R,
"SW1, SW2",SW_SPST_Omron_B3FS-101xP,2,SW_Omron_B3FS,
U1,TFBGA-100_8x8mm_Layout10x10_P0.8mm,1,STM32H743VIH6,
"U10, U7, U8, U9",SOIC-8_3.9x4.9mm_P1.27mm,4,SI4116DY-T1-GE3,
"U11, U13",SOT-563,2,AP62150Z6,
U12,TSOP-5_1.65x3.05mm_P0.95mm,1,NCV4296-2CSN50T1G,
U14,SON127P600X800X80-9N,1,W25Q256JVEIQ_TR,
U2,SOT95P280X110-6N,1,TPS565208DDCR,
U3,DFN-6-1EP_2x2mm_P0.65mm_EP1x1.6mm,1,NCV68261,
U4,LGA-14_3x2.5mm_P0.5mm_LayoutBorder3x4y,1,LSM6DSO,
U5,SOT-23-6,1,USBLC6-2SC6,
U6,ST_HLGA-10_2x2mm_P0.5mm_LayoutBorder3x2y,1,LPS22HB,
Y1,Crystal_SMD_5032-4Pin_5.0x3.2mm,1,ABM3B-8.000MHZ-B2-T,
